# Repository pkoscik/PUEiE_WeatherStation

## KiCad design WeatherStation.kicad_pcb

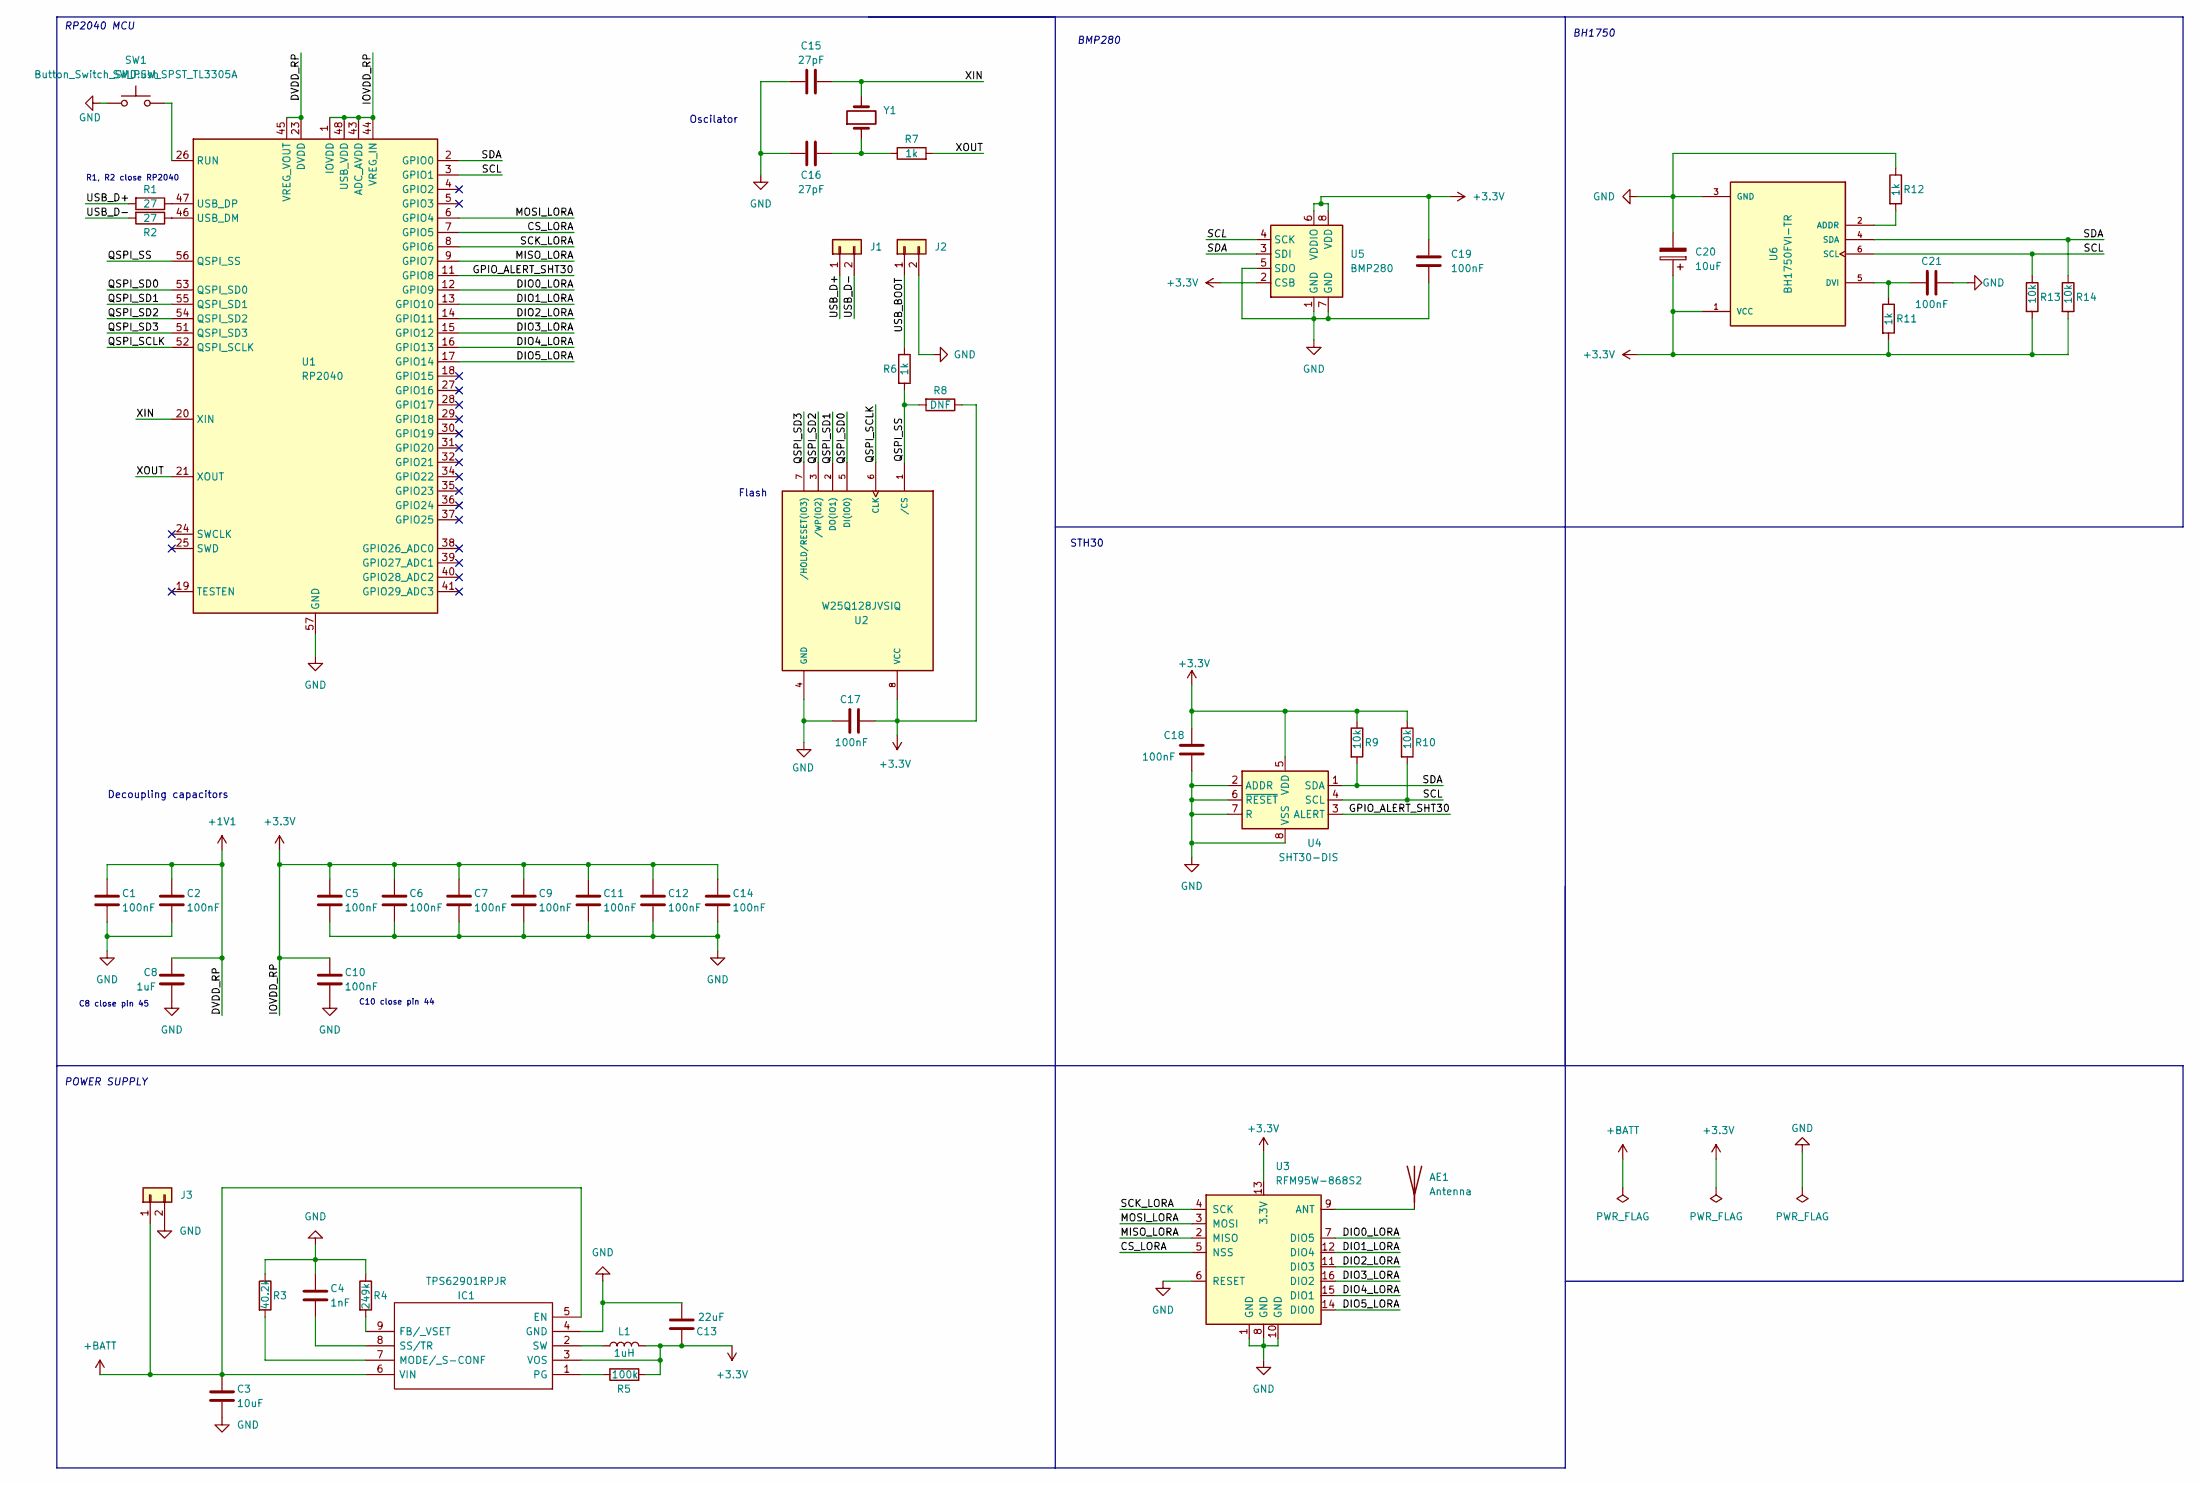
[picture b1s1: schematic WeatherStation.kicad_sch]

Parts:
AE1: Antenna; SMA_Amphenol_901-144_Vertical
C1, C2, C5, C6, C7, C9, C10, C11, C12, C14, C17, C18, C19, C21: 100nF; C_0603_1608Metric_Pad1.08x0.95mm_HandSolder
C3, C20: 10uF; C_0603_1608Metric_Pad1.08x0.95mm_HandSolder
C4: 1nF; C_0603_1608Metric_Pad1.08x0.95mm_HandSolder
C8: 1uF; C_0603_1608Metric_Pad1.08x0.95mm_HandSolder
C13: 22uF; C_0603_1608Metric_Pad1.08x0.95mm_HandSolder
C15, C16: 27pF; C_0603_1608Metric_Pad1.08x0.95mm_HandSolder
IC1: TPS62901RPJR; Manufacturer_Part_Number TPS62901RPJR; Mouser Part Number 595-TPS62901RPJR
J1, J2, J3: Conn_01x02; PinHeader_1x02_P2.54mm_Vertical
L1: 1uH; L_0603_1608Metric_Pad1.05x0.95mm_HandSolder
R1, R2: 27; R_0603_1608Metric_Pad0.98x0.95mm_HandSolder
R3: 40.2k; R_0603_1608Metric_Pad0.98x0.95mm_HandSolder
R4: 249k; R_0603_1608Metric_Pad0.98x0.95mm_HandSolder
R5: 100k; R_0603_1608Metric_Pad0.98x0.95mm_HandSolder
R6, R7, R11, R12: 1k; R_0603_1608Metric_Pad0.98x0.95mm_HandSolder
R8: DNF; R_0603_1608Metric_Pad0.98x0.95mm_HandSolder
R9, R10, R13, R14: 10k; R_0603_1608Metric_Pad0.98x0.95mm_HandSolder
SW1: SW_Push; SW_SPST_TL3305A
U1: RP2040; QFN-56-1EP_7x7mm_P0.4mm_EP3.2x3.2mm
U2: W25Q128JVSIQ; SOIC127P790X216-8N; PARTREV I
U3: RFM95W-868S2; HOPERF_RFM9XW_SMD
U4: SHT30-DIS; Sensirion_DFN-8-1EP_2.5x2.5mm_P0.5mm_EP1.1x1.7mm
U5: BMP280; Bosch_LGA-8_2x2.5mm_P0.65mm_ClockwisePinNumbering
U6: BH1750FVI-TR; XDCR_BH1750FVI-TR; PARTREV D
Y1: Crystal; Crystal_SMD_HC49-SD_HandSoldering

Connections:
+1V1: C1.1, C2.1, C8.1, U1.23 (DVDD), U1.45 (VREG_VOUT), U1.50 (DVDD)
+3.3V: C5.1, C6.1, C7.1, C9.1, C10.1, C11.1, C12.1, C13.1, C14.1, C17.2, C18.1, C19.1, C20.1, IC1.3 (VOS), L1.2, R5.2, R8.1, R9.1, R10.1, R11.2, R13.2, R14.2, U1.1 (IOVDD), U1.10 (IOVDD), U1.22 (IOVDD), U1.33 (IOVDD), U1.42 (IOVDD), U1.43 (ADC_AVDD), U1.44 (VREG_IN), U1.48 (USB_VDD), U1.49 (IOVDD), U2.8 (VCC), U3.13 (3.3V), U4.5 (VDD), U5.2 (CSB), U5.6 (VDDIO), U5.8 (VDD), U6.1 (VCC)
+BATT: C3.1, IC1.5 (EN), IC1.6 (VIN), J3.1
/CS_LORA: U1.7 (GPIO5), U3.5 (NSS)
/DIO0_LORA: U1.12 (GPIO9), U3.7 (DIO5)
/DIO1_LORA: U1.13 (GPIO10), U3.12 (DIO4)
/DIO2_LORA: U1.14 (GPIO11), U3.11 (DIO3)
/DIO3_LORA: U1.15 (GPIO12), U3.16 (DIO2)
/DIO4_LORA: U1.16 (GPIO13), U3.15 (DIO1)
/DIO5_LORA: U1.17 (GPIO14), U3.14 (DIO0)
/GPIO_ALERT_SHT30: U1.11 (GPIO8), U4.3 (ALERT)
/MISO_LORA: U1.9 (GPIO7), U3.2 (MISO)
/MOSI_LORA: U1.6 (GPIO4), U3.3 (MOSI)
/QSPI_SCLK: U1.52 (QSPI_SCLK), U2.6 (CLK)
/QSPI_SD0: U1.53 (QSPI_SD0), U2.5 (DI(IO0))
/QSPI_SD1: U1.55 (QSPI_SD1), U2.2 (DO(IO1))
/QSPI_SD2: U1.54 (QSPI_SD2), U2.3 (/WP(IO2))
/QSPI_SD3: U1.51 (QSPI_SD3), U2.7 (/HOLD/RESET(IO3))
/QSPI_SS: R6.2, R8.2, U1.56 (QSPI_SS), U2.1 (/CS)
/SCK_LORA: U1.8 (GPIO6), U3.4 (SCK)
/SCL: R10.2, R13.1, U1.3 (GPIO1), U4.4 (SCL), U5.4 (SCK), U6.6 (SCL)
/SDA: R9.2, R14.1, U1.2 (GPIO0), U4.1 (SDA), U5.3 (SDI), U6.4 (SDA)
/USB_BOOT: J2.1, R6.1
/USB_D+: J1.1, R1.2
/USB_D-: J1.2, R2.2
/XIN: C15.2, U1.20 (XIN), Y1.2
/XOUT: R7.2, U1.21 (XOUT)
GND: C1.2, C2.2, C3.2, C4.1, C5.2, C6.2, C7.2, C8.2, C9.2, C10.2, C11.2, C12.2, C13.2, C14.2, C15.1, C16.1, C17.1, C18.2, C19.2, C20.2, C21.2, IC1.4 (GND), J2.2, J3.2, R3.1, R4.1, R12.1, SW1.1, U1.57 (GND), U2.4 (GND), U3.1 (GND), U3.6 (RESET), U3.8 (GND), U3.10 (GND), U4.2 (ADDR), U4.6 (~RESET), U4.7 (R), U4.8 (VSS), U4.9 (VSS), U5.1 (GND), U5.5 (SDO), U5.7 (GND), U6.3 (GND)
unnamed: AE1.1 (A), U3.9 (ANT)
unnamed: C4.2, IC1.8 (SS/TR)
unnamed: C16.2, R7.1, Y1.1
unnamed: C21.1, R11.1, U6.5 (DVI)
unnamed: IC1.1 (PG), R5.1
unnamed: IC1.2 (SW), L1.1
unnamed: IC1.7 (MODE/_S-CONF), R3.2
unnamed: IC1.9 (FB/_VSET), R4.2
unnamed: R1.1, U1.47 (USB_DP)
unnamed: R2.1, U1.46 (USB_DM)
unnamed: R12.2, U6.2 (ADDR)
unnamed: SW1.2, U1.26 (RUN)

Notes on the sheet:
STH30
Flash
R1, R2 close RP2040
C10 close pin 44
Oscilator
C8 close pin 45
BH1750
RP2040 MCU
BMP280
Decoupling capacitors
POWER SUPPLY

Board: 2 copper layers, 49 parts (0 on the bottom side), 40 nets, no tracks yet.

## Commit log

2022-11-13 some capatitiors and sensors
2022-11-21 kabelki
2022-11-21 PCB lets gooo
2022-12-05 Some puzzle
2022-12-11 PCB layout update
